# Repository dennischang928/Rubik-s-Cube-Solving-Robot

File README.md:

# Rubik's-Cube-Solving-Robot

# Abstract

   Rubik's Cube, a 3-D combination puzzle invented by Ernő Rubik in 1974, is the World’s top-selling puzzle game and best-selling toy. Rubik's Cube is surprisingly complex, there are 43,252,003,274,489,856,000 permutations of a standard 3×3×3 Rubik's Cube. Although humans are impossible to memorize all permutations of a Rubik’s Cube, humans can solve the puzzle as fast as 3.47 seconds. In recent years, a robot developed by MIT students can solve it in 0.38 seconds using an optimal algorithm.
   In this project, I developed a Rubik’s Cube-solving robot using a Computer Vision algorithm from scratch. The robot has 4 stepper motors and 4 servo motors as actuators. A camera is included to observe each color arrangement of the face of the Cube in a scrambled state sequentially. The image that the camera observed will be sent through a serial interface to the computer. I implement a solving algorithm that will take the Cube state as input and the sequence of moves that solve the Cube as an output. The sequence of moves is sent to the MCU and is then translated into a series of instructions. The stepper motors and the servo motors then work together to twist the Cube according to the instructions, fully solving the Cube.

# Contents

- Abstract
- Motivation
- Introduction
- Materials
- Designs
    - Hardware
        - Actuators
        - Camera
        - Electronics
    - Programming
        - Computer vision
        - Thistlethwaite's algorithm
        - Firmware
- Challenges and Conclusion
- Reference
- Appendix — Workflow of the Rubik's Cube solving robot

# Motivation

   In recent years, Computer Vision becomes more popular. Computer Vision has a lot of applications, such as object detection, event detection, video tracking, and color recognition. To familiarize myself in the field, I decide to develop a robot that solves a Rubik’s Cube using Computer Vision.
   The goal is to fully solve a Rubik’s cube by twisting it using clamps attached to stepper and Servo motors. We will use a camera to capture each face of the cube. A computer will then be used, using the computer vision algorithm, to process these images and find out the color of the 9 stickers in each face. Once the color states of the cube are determined, the computer can then compute the sequence of moves that fully solve the cube.

# Introduction

I design the robot using Fusion 360 and Eagle. This robot consists of 4 stepper and Servo motors, 4 pairs of 3d-printed clamp and frame, a camera, and a PCB board with a microcontroller and 4 stepper motor drivers

The design of the robot ^

To know the initial state of the Cube, I use a camera to capture the color of the Cube. Since the camera can only capture a single face of the Cube each time, the robot needs to rotate the Cube for the camera to capture all the faces of the cube. // After capturing, the camera is going to send those images to the computer through a USB port. //

The computer will then detect the position and orientation of each face from all 6 images. By using these information, the computer can find out the position and area of each sticker of the Cube in those images. The computer can now extract the color of each sticker, and determine the color of each sticker using computer vision.

Once the initial state of the Cube is found, the computer solves the Cube using Thistlethwaite's algorithm. The solution, the sequence of moves represented in Rubik's Cube Notation, will then be sent from the computer to the microcontroller. Afterwards, the microcontroller translates these notations into a series of stepper and Servo motors movements that twist the Cube and fully solving the Cube.

# Materials

- 4 stepper and Servo motors
- 4 3d-printed clamps attached to the stepper motors
- An Arduino nano and 4 stepper motor drivers
- A DC transformer
- A fill light

# Designs

## Hardware

### Actuators

To physically twist and rotate the cube, I use 4 NEMA 17 stepper motors that use a clamp to clip and twist 4 individual faces of the cube. I have considered using DC motors and brushless motors, but both of them can't know their physical rotated-angle without an encoder, so they can't twist the cube precisely.

I have considered using DC motors and brushless motors, but both of them can't twist the Cube precisely because their physical rotated-angle cannot be determined without an encoder.

Although Servo motors can rotate precisely to an angle, most Servo motors can only rotate from 0 degrees to 180 degrees. <add a reason why 0-180 is bad> Therefore, I decided to use stepper motors because they are continuous(they can rotate in one direction infinitely) and can rotate precisely. Therefore, a stepper motor will perfectly fit our use case.

Stepper motors operate using a coil to attract the permanent magnets that encircle the center axle. By energizing the coils, the axle of the motor can rotate precisely by 1.8 degrees. (Stepper motors take 200 steps to make a complete rotation, so its resolution is 1.8 degree = (360° /200 steps))

Stepper motors move in steps. For example, a stepper motor with 200 steps resolution will rotate 1.8 degrees angle for one step (360° / 200 steps).

Simplified stepper motor rotates 3 steps.

Stepper motor is an Open Loop Control System, we don't know its position upon start-up. 

In order to twist the Cube properly, the clamp needs to be aligned vertically with the Cube. Therefore, I design a device that uses a light sensor to provide feedback for the motor to align the clamp and the cube. The device consists of a disk attached to the axle of the motor and a light sensor facing the disk. The cube and clap are in perfect alignment when the light sensor faces the hole directly. Hence, by reading the sensor value, the motor can rotate the clamp until it aligns perfectly with the cube.

that has a disc with a hole and a light sensor 

Fig 1

I found a problem when the clamp is twisting the cube. If one of the clamps rotates horizontal, the clamps on its left and right can't twist the cube because the clamp that is horizontal blocks their rotation. Tj is also a Servo motor that is responsible to separate the clamp from the cube so that all clamps can rotate freely. As shown in the image on the left

In contrast to the stepper motor, Servo motor is a Closed Loop control system. When the Servo motor is moving, the position given by the potentiometer as feedback (Fig 1)
is sent to the Servo motor control board to ensure it rotates to the expected position.

I use Rack and pinion mechanics to convert the rotational motion of the Servo motor into linear motion to separate the clamp from the cube.

### Camera

To determine the initial state of a Rubik's cube, I use a camera to capture the color of each face of the Rubik's cube. I chose a Logitech  Webcam as the camera because it has HD resolution and an autofocus function. Moreover, the camera allows you to adjust the brightness, sharpness, contrast, and saturation of the image. By adjusting these values, the images will become sharper and easier for the computer to distinguish colors.

Trying to distinguish color from the image that the camera sends to the computer, I find that if the ambient light around the cube is unstable, the color recognition program will be extremely inaccurate. To make sure the projected light on the cube is consistent, I added an artificial light source to maintain the brightness of the image. Therefore, I use 4 LED strings to supply light in 4 directions, so the brightness anywhere on the face of the cube is the same.

### Electronics

Instead of using a commercial CNC control board that can control stepper motors easily, I am going to design my robot controller PCB that can control 4 stepper motors and 4 Servo motors of my robot because most commercial CNC control boards can't control 2 or more Servo motors. Also, there is a lot of limitations of programming these commercial PCB board, so I decided to make my own control board.

Robot control board

- Microcontroller

In order to control the whole robot, I decided to use Arduino nano to control the whole system because it is smaller than Arduino UNO and easy to program. Arduino Nano has a built-in Mini USB jack, so it can communicate with the computer through a Serial port with the Mini USB jack.

- Stepper motor Control

Although stepper motors have a lot of advantages, controlling stepper motors often require sufficient and controlled energy for phases in a precise sequence, so a driver is often needed. Due to this, I plan to use 4 A4988 stepper motor drivers to control all of my stepper motors of the robot.

Each A4988 motor driver required 2 control signal pins (step, direction) and 3 setup signal pins(MS1, MS2, MS3). The step and direction pins are used to control the movement of the stepper motors. The direction pin controls the rotate direction of the motor, and we can control the movement of a step of the motor by sending a pulse to the step pin. The MS1, MS2, MS3 pins are used to control the step of the stepper motor. By changing the input state of these pins to logic low or logic high, you can select one of the five steps resolution according to the table(Fig 2).

Fig 2

- Servo motors Control

A Servo motor can be controlled by sending a series of pulses through the signal pin. By changing the width of these pulses, we can control the Servo motor rotates to different angles.

How pulses with different width control the Servo motor

## Programming

### Computer visions

   In order to determine the color arrangement of each of the image that captured by the camera precisely, I implemented a method that can found out the difference of two colors.
   A color model is a visualization that depicts the color spectrum as a multidimensional model. There are some commonly used color models in the world. Most modern color models have 3 dimensions (like RGB and HSV), while other models have more dimensions (like CMYK), and I am going to compare these different color models and found out which of them are more reliable in this project.

---

- RGB
    
    RGB is a 3-dimensional color model. RGB color model represents a color by mixing three different colors (Red, Green, and Blue). Although RGB color model is commonly used in our daily life, RGB color model is a non-uniform color model, which means the Euclidian distance of two colors represented by the RGB color model does not correspond to the color difference perceived by humans.
    
    *Euclidian distance:*
    
    $distance=√((R2−R1)^2+(G2−G1)^2+(B2−B1)^2)$

---

- HSV
    
    HSV is a cylindrical color model that remaps the RGB primary colors into dimensions that are easier for humans to understand.
    
    In HSV color model, we can represent a color with 3 variables (Hue, Saturation, Value). Hue controls the angle of the color on the RGB color circle; Saturation controls the amount of color used; Value controls the brightness of the color.

    HSV (cylindrical color model)

---

- CIELAB
    
    CIELAB color model is three-dimensional, you can represent a color with 3 variables in CIELAB color model while L stands for perceptual lightness, and A and B stand for the four unique colors of human vision: red, green, blue, and yellow. In short, CIELAB is designed to approximate human vision, so it can describe a color more accurate than RGB and HSV color model can.

    CIELAB color space top view

According to the comparison, I think using CIELAB color model in the Computer Vision method has a lot of advantages, so I plan to use CIELAB color model to represent a color in the Computer Vision method.

When the computer wants to distinguish which color (orange, white, blue, red, yellow, green) of a sticker is, the most important thing is to find out the distance between the sticker pixel color and the reference colors, so the computer can then compare the distance between these reference colors, and distinguish the color. In order to get the color difference between two colors reliably, I use a CIEDE2000 ΔE method instead of the Euclidean distance method because the CIEDE2000 ΔE method is more reliable for human vision.

Given a reference color (L*1, a*1, b*1) and another color (L*2, a*2, b*2), the CIEDE2000 difference of these 2 colors is:

CIEDE2000 ΔE formula 
[https://en.wikipedia.org/wiki/Color_difference](https://en.wikipedia.org/wiki/Color_difference)

Where:

[https://wikimedia.org/api/rest_v1/media/math/render/svg/2940920f995d52312ede05214ffa3c60f0db9b7f](https://wikimedia.org/api/rest_v1/media/math/render/svg/2940920f995d52312ede05214ffa3c60f0db9b7f)

CIEDE2000 ΔE formula 
[https://en.wikipedia.org/wiki/Color_difference](https://en.wikipedia.org/wiki/Color_difference)

Because of the rotation of the cube, the cube position may always shift when scanning the cube, so I have to frequently adjust the cube detect area of the camera manually before scanning it, and I think that adjusting the cube manually is annoying, especially when I  debugging the program.

Then, I try to implement a cube position tracking program in the solver, so that the solver can adjust the detect area automatically.

The tracking program is actually dum. First of all, the program is going to make the dimmer place of the image more dimmer; the brighter place brighter. The program can then find out the position of the centerpiece of the cube by comparing the pixel of the filtered image. The program can then find out the position of other pieces.

Image before filter

Filtered image

### Thistlethwaite's algorithm

After finding the state of the cube, the computer will then solve the cube using Thistlethwaite's algorithm. Thistlethwaite's algorithm is a famous algorithm devised by Morwen B. Thistlethwaite.

Before I explain how the algorithm works, we first have to know how do people represent a twist of a cube. People usually use a notation called Rubik's Cube Notation to represent a twist of a cube. The twist of a Rubik's Cube is classified into three categories of Notations (clockwise twist, counterclockwise twist, double clockwise twist).

- The notation with only one letter refers to a clockwise face twist in 90 degrees (quarter turn). "F" refers to a clockwise turn of the Front face in 90 degrees.
- The notation with one letter followed by an apostrophe (') refers to a counterclockwise face twist in 90 degrees (quarter turn). "D'" refers to a counterclockwise turn of the Down face in 90 degrees.
- The notation with one letter followed by the number 2 refers to a clockwise face twist in 180 degrees (double turn). "U2" refers to a clockwise turn of the Up face in 180 degrees.

Thistlethwaite algorithm solves a cube by twisting the cube by a certain set of moves. When the cube reaches a specific state, the cube will "move" from one "group" to another. As the cube reaches another "group", the set of moves of the cube will change and the cube will be easier to solve computationally.

The groups are:

- Group 0:

[https://wikimedia.org/api/rest_v1/media/math/render/svg/2dbdffdebca6e844bdf3c7548a8033992ef6ac79](https://wikimedia.org/api/rest_v1/media/math/render/svg/2dbdffdebca6e844bdf3c7548a8033992ef6ac79)

Required Cube state: This group contains all possible states of the Rubik's Cube.

---

- Group 1:

[https://wikimedia.org/api/rest_v1/media/math/render/svg/116b5e3559d97ddaa688362537461712c1435f10](https://wikimedia.org/api/rest_v1/media/math/render/svg/116b5e3559d97ddaa688362537461712c1435f10)

Required Cube state: All 12 edge pieces are correctly oriented.

After reaching Group 1, The cube can then be solved without using U and D turns.

---

- Group 2:

[https://wikimedia.org/api/rest_v1/media/math/render/svg/ab29e5a1ef0d23014458f9603f6c108b7aec73a6](https://wikimedia.org/api/rest_v1/media/math/render/svg/ab29e5a1ef0d23014458f9603f6c108b7aec73a6)

Required Cube state: All corner pieces are correctly oriented. Also, four of the edge pieces are moved to the correct slice: the front-up, front-down, back-up, and back-down edge pieces are placed in the M slice.

After reaching Group 2, The cube can then be solved without using F, B, U, and D moves.

---

- Group 3:

[https://wikimedia.org/api/rest_v1/media/math/render/svg/b9990ca7e1121afb33509d738d77f1d0c455be62](https://wikimedia.org/api/rest_v1/media/math/render/svg/b9990ca7e1121afb33509d738d77f1d0c455be62)

Required Cube state: All corner pieces are moved to the correct orbit. (A corner is in the correct orbit if it can be moved to its home position with only 180-degree twists.) Also, each edge piece is moved to its home slice.

At that point, the cube can be solved with only 180 degrees turn.

---

- Group 4:

[https://wikimedia.org/api/rest_v1/media/math/render/svg/27929bbe730561ca9eb1540e72756b5674436bb5](https://wikimedia.org/api/rest_v1/media/math/render/svg/27929bbe730561ca9eb1540e72756b5674436bb5)

The final group requires only one state, which is a solved cube.

### Firmware

In this project, I use Arduino nano board as my microcontroller to control the stepper motors and servo motors. I implement an Arduino stepper motor driver library in the Arduino board to control the movement of the Stepper motors. For the Servo motors, I use an Arduino built-in Servo library to control them.

There is a lot of ways to communicate between the computer and the Arduino board, such as I2C, Serial communication, and SPI. I decided to use the Serial communication way because it is widely used in the Arduino board (Every Arduino board has its own Serial port). For an Arduino Nano board, it has a built-in mini-USB jack

Here is a case of communication:

The Computer aims to twist the Cube in U U2 D2:

**Step 1:** The computer sends a command("U U2 D2") to the Solver through the Serial interface.

**Step 2:** The Solver receives the command and controls the Stepper motors and the Servo motors to twist the Cube according to the command.

**Step 3:** After twisting the cube, the Solver will send a signal to the computer. Let the computer knows that it has done the task.

# Challenges and Conclusion

After assembled the Solver, there are some problems that I have experienced. When designing this robot, I aim to use a magnetic encoder to monitor the position of the Stepper motor. After I fully assembled the Solver, I try to read the value of the magnetic encoders by connecting them in parallel using I2C, but then I found that these magnetic encoders have the same I2C addresses, and I can't change the addresses. Therefore, the microcontroller can't read the values of them using I2C, so I have redesigned the robot, and I use a light sensor as the position monitoring sensor instead of a magnetic sensor.

There are also some challenges that I have gone through when I programming the robot, such as the inaccuracy of the color detection. To fix the issue, I add an artificial light source to stabilize the light condition of the cube.

The robot also experienced some issues when the stepper motor rotate. Because the stepper motor provides no feedback to the microcontroller,  the stepper motor can't affirm a perfect 90 degrees twist is executed. Also, there are gaps between the clamp and the Cube, so there will be some degrees of error when twisting the cube. As a result, slight errors accumulated in the alignment of the Cube after a twist. Because of the alignment of the Cube, the rotation of the stepper motor may be stuck, but the stepper motor can't realize that it is stuck, and it will keep executing the following twists.

Were I to continue work on this project, the following attributes would be changed:

- A Feedback would be added to affirm a perfect 90 degrees twist is executed
- Reduce the size of the Robot.
- Design an adjustable clamp, so that the solver can fit any size of 3*3 Rubik's Cube.

# Appendix — Workflow of the Rubik's Cube solving robot:

Rubik's Cube Solving Robot test:
[https://youtu.be/ZOZHCysa5HY](https://youtu.be/ZOZHCysa5HY)

# Reference

- Color models and color spaces [https://programmingdesignsystems.com/color/color-models-and-color-spaces/](https://programmingdesignsystems.com/color/color-models-and-color-spaces/)
- Color difference - Wikipedia [https://en.wikipedia.org/wiki/Color_difference](https://en.wikipedia.org/wiki/Color_difference)
- How to control stepper motor with A4988 driver and Arduino [https://howtomechatronics.com/tutorials/arduino/how-to-control-stepper-motor-with-a4988-driver-and-arduino/](https://howtomechatronics.com/tutorials/arduino/how-to-control-stepper-motor-with-a4988-driver-and-arduino/)
- jeswiezy_Project_Final_Report
[http://web.mit.edu/6.111/www/f2017/projects/jeswiezy_Project_Final_Report.pdf](http://web.mit.edu/6.111/www/f2017/projects/jeswiezy_Project_Final_Report.pdf)
- Thistlethwaite's 52-move algorithm
[https://www.jaapsch.net/puzzles/thistle.htm](https://www.jaapsch.net/puzzles/thistle.htm)
- Rubik’s Cube Reconstruction from Single View for Service Robots
[https://www.ia.pw.edu.pl/~wkasprza/PAP/ICCVG06.pdf](https://www.ia.pw.edu.pl/~wkasprza/PAP/ICCVG06.pdf)
- All About Stepper Motors
[https://learn.adafruit.com/all-about-stepper-motors/what-is-a-stepper-motor](https://learn.adafruit.com/all-about-stepper-motors/what-is-a-stepper-motor)

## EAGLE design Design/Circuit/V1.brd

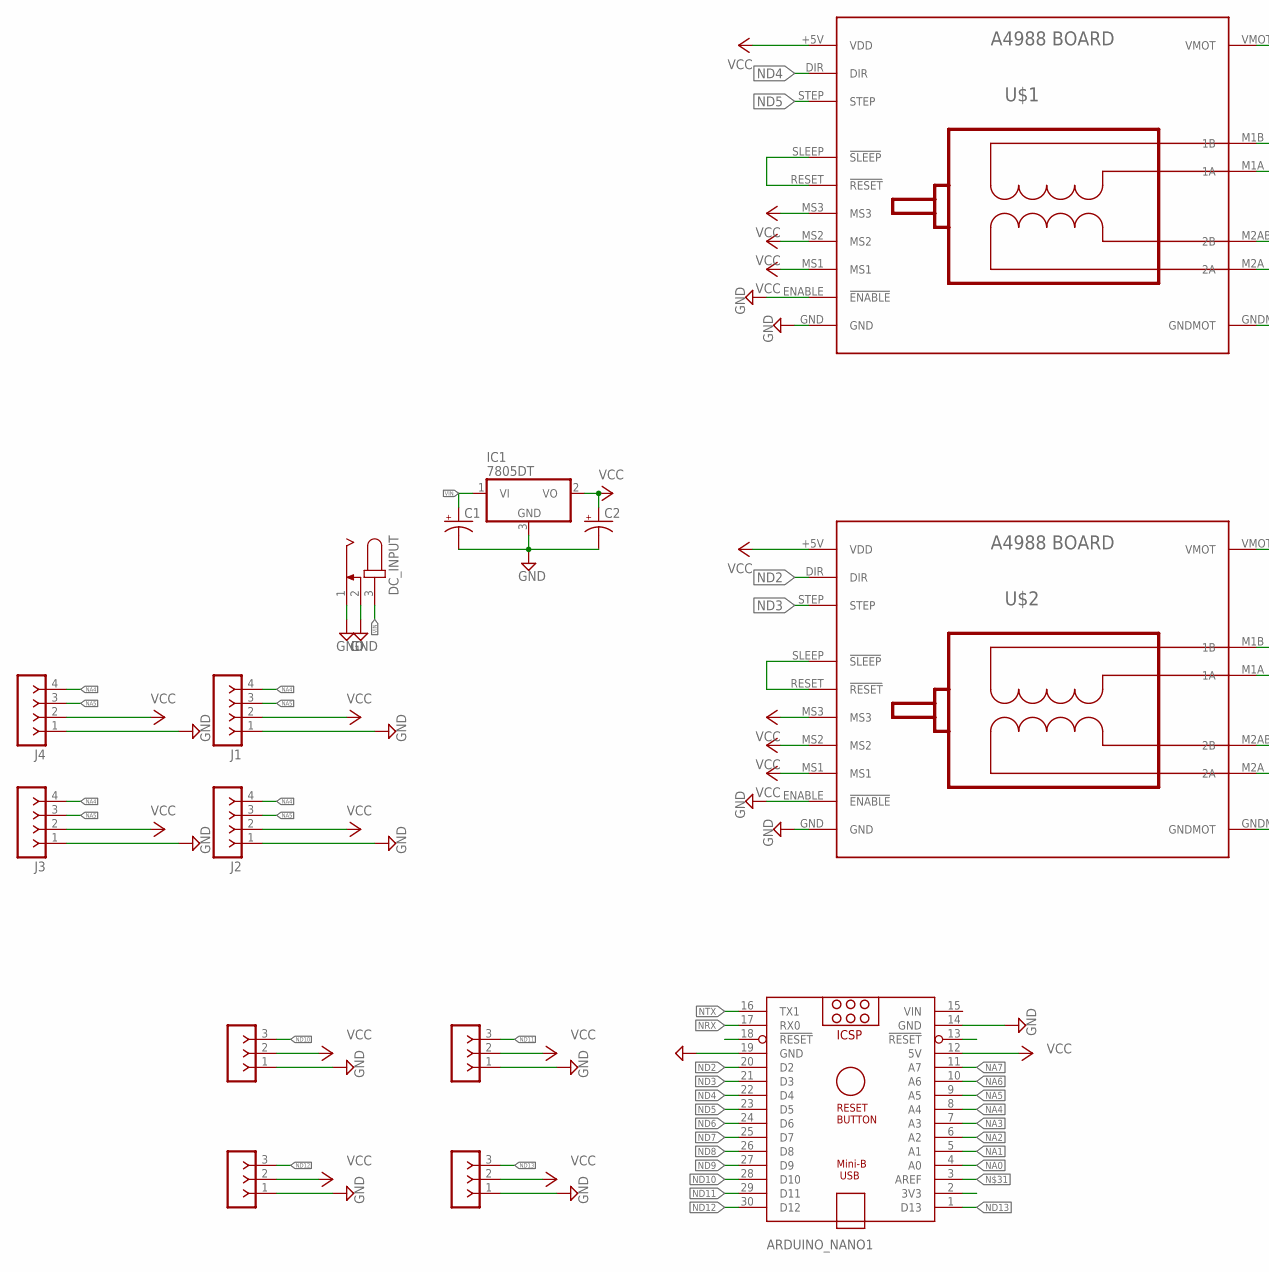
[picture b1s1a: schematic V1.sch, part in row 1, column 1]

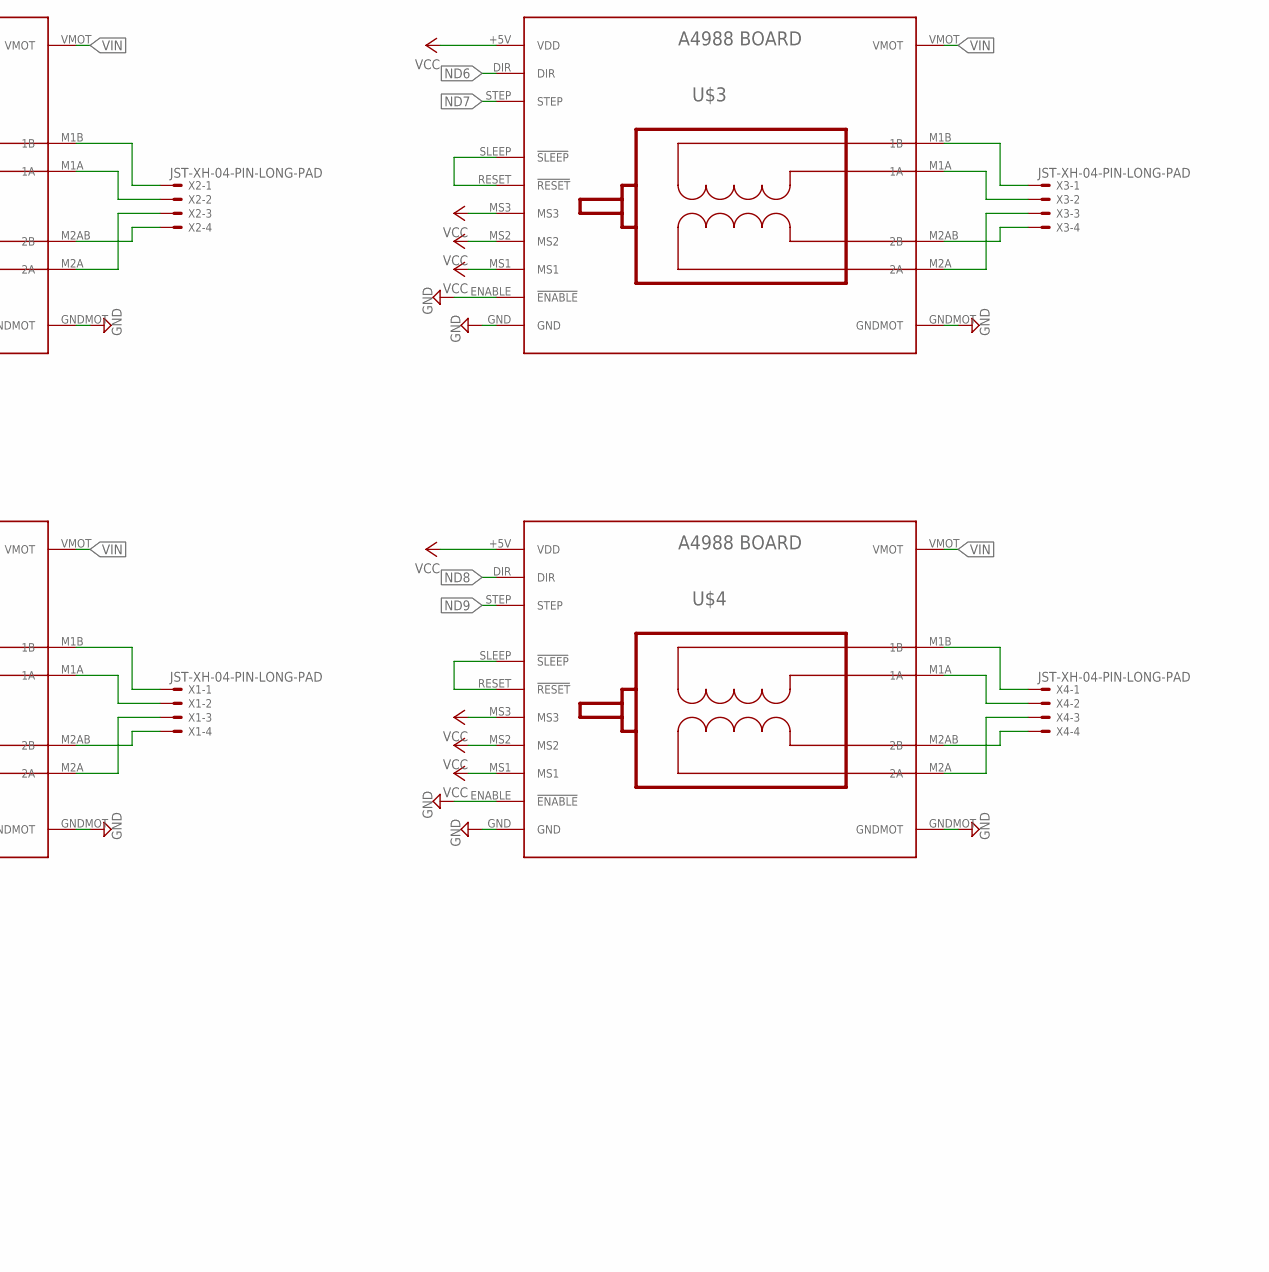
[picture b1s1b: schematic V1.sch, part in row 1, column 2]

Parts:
ARDUINO_NANO1: ARDUINO_NANO
C1, C2: CPOL-USE2.5-5; E2,5-5
DC_INPUT: JACK-PLUG0; SPC4077
IC1: 7805DT; TO252
J1, J2, J3, J4: F-1X04-SIP-100-40; SIP-100-04-40
SERVO1, SERVO2, SERVO3, SERVO4: F-1X03-SIP-100-40; SIP-100-03-40
U$1, U$2, U$3, U$4: BOARD_A4988
X1, X2, X3, X4: JST-XH-04-PIN-LONG-PAD; JST-XH-04-PACKAGE-LONG-PAD

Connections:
GND: ARDUINO_NANO1.14 (GND), ARDUINO_NANO1.19 (GND), C1.-, C2.-, DC_INPUT.1, DC_INPUT.2, IC1.3 (GND), J1.1, J2.1, J3.1, J4.1, SERVO1.1, SERVO2.1, SERVO3.1, SERVO4.1, U$1.ENABLE (!ENABLE), U$1.GND, U$1.GNDMOT, U$2.ENABLE (!ENABLE), U$2.GND, U$2.GNDMOT, U$3.ENABLE (!ENABLE), U$3.GND, U$3.GNDMOT, U$4.ENABLE (!ENABLE), U$4.GND, U$4.GNDMOT
unnamed: U$2.M1B (1B), X1.1
unnamed: U$2.M1A (1A), X1.2
unnamed: U$2.M2A (2A), X1.3
unnamed: U$2.M2AB (2B), X1.4
unnamed: U$1.M1B (1B), X2.1
unnamed: U$1.M1A (1A), X2.2
unnamed: U$1.M2A (2A), X2.3
unnamed: U$1.M2AB (2B), X2.4
unnamed: U$2.RESET (!RESET), U$2.SLEEP (!SLEEP)
unnamed: U$1.RESET (!RESET), U$1.SLEEP (!SLEEP)
unnamed: U$3.M1B (1B), X3.1
unnamed: U$3.M1A (1A), X3.2
unnamed: U$3.M2A (2A), X3.3
unnamed: U$3.M2AB (2B), X3.4
unnamed: U$3.RESET (!RESET), U$3.SLEEP (!SLEEP)
unnamed: U$4.M1B (1B), X4.1
unnamed: U$4.M1A (1A), X4.2
unnamed: U$4.M2A (2A), X4.3
unnamed: U$4.M2AB (2B), X4.4
unnamed: U$4.RESET (!RESET), U$4.SLEEP (!SLEEP)
NA0: ARDUINO_NANO1.4 (A0)
NA1: ARDUINO_NANO1.5 (A1)
NA2: ARDUINO_NANO1.6 (A2)
NA3: ARDUINO_NANO1.7 (A3)
NA4: ARDUINO_NANO1.8 (A4), J1.4, J2.4, J3.4, J4.4
NA5: ARDUINO_NANO1.9 (A5), J1.3, J2.3, J3.3, J4.3
NA6: ARDUINO_NANO1.10 (A6)
NA7: ARDUINO_NANO1.11 (A7)
ND2: ARDUINO_NANO1.20 (D2), U$2.DIR
ND3: ARDUINO_NANO1.21 (D3), U$2.STEP
ND4: ARDUINO_NANO1.22 (D4), U$1.DIR
ND5: ARDUINO_NANO1.23 (D5), U$1.STEP
ND6: ARDUINO_NANO1.24 (D6), U$3.DIR
ND7: ARDUINO_NANO1.25 (D7), U$3.STEP
ND8: ARDUINO_NANO1.26 (D8), U$4.DIR
ND9: ARDUINO_NANO1.27 (D9), U$4.STEP
ND10: ARDUINO_NANO1.28 (D10), SERVO1.3
ND11: ARDUINO_NANO1.29 (D11), SERVO2.3
ND12: ARDUINO_NANO1.30 (D12), SERVO3.3
ND13: ARDUINO_NANO1.1 (D13), SERVO4.3
NRX: ARDUINO_NANO1.17 (RX0)
NTX: ARDUINO_NANO1.16 (TX1)
VCC: ARDUINO_NANO1.12 (5V), C2.+, IC1.2 (VO), J1.2, J2.2, J3.2, J4.2, SERVO1.2, SERVO2.2, SERVO3.2, SERVO4.2, U$1.+5V (VDD), U$1.MS1, U$1.MS2, U$1.MS3, U$2.+5V (VDD), U$2.MS1, U$2.MS2, U$2.MS3, U$3.+5V (VDD), U$3.MS1, U$3.MS2, U$3.MS3, U$4.+5V (VDD), U$4.MS1, U$4.MS2, U$4.MS3
VIN: ARDUINO_NANO1.15 (VIN), C1.+, DC_INPUT.3, IC1.1 (VI), U$1.VMOT, U$2.VMOT, U$3.VMOT, U$4.VMOT

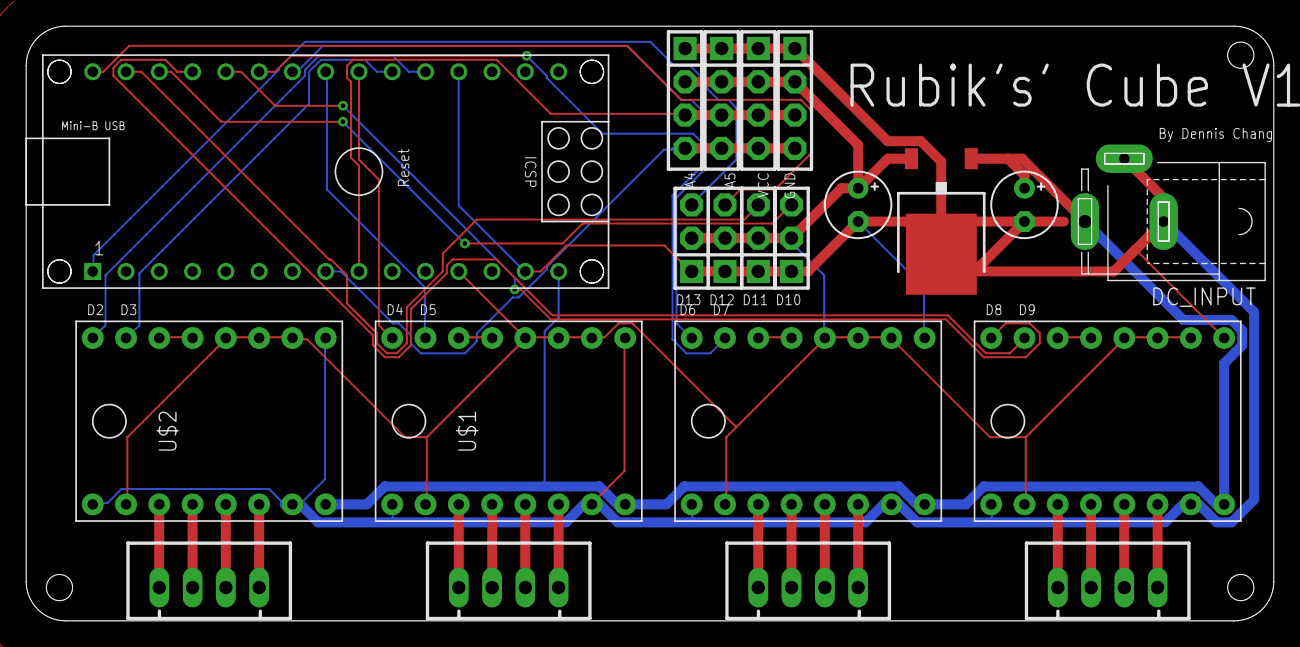
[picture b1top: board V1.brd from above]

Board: 2 copper layers, 95.2 x 45.4 mm, 21 parts (0 on the bottom side), 37 nets.

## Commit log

2021-10-05 Rename Paper 0d67a40c9a844161bf0b6c94b4b3c9c2.md to README
2021-10-05 Rename README to README.md
2021-10-05 Added README.md
    Added README.md and its resource files
2021-10-05 Fix the "freely. As' vLinking
2021-10-05 Added a title "Rubik's-Cube-Solving-Robot"

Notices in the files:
parts and their libraries:
con-headers-jp: Copyright (C) 2008, Bob Starr
